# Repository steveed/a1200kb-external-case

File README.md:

# A1200KB external case

Run an [A1200KBv2](https://github.com/aeberbach/A1200KBv2) mechanical keyboard in its own external case, connected by cable to an A1200 motherboard in a case with no built-in keyboard, such as the Checkmate 1500 Plus.

Normally an external case means a PS/2 or USB keyboard and an adapter. This project keeps the real A1200 keyboard instead.

**Setting one up, or stuck?** The [setup guide](docs/Readme.md) shows each way of connecting, what (if anything) has to change on the A1200, the cable wiring, and a troubleshooting table.

## How it works

The A1200 keyboard has no controller of its own. It is a bare switch matrix scanned by the keyboard controller on the motherboard, so every one of the 31 lines on the keyboard ribbon (FFC) has to reach the motherboard. DB25 has too few pins, so this uses DB37:

```
A1200 motherboard ── FFC ── [adapter] ══ DB37 cable ══ [adapter] ── FFC ── A1200KBv2 keyboard
     LED header ──────────── J2                         J2 ──────────────── keyboard LED header
```

Both ends use the same adapter board. See [`adapter/Readme.md`](adapter/Readme.md) for the pinout, build options and parts.

### Alternative: standard Amiga keyboard (DIN 5)

On A1200 boards with the CN17 "KB TEST" header, the keyboard controller's serial lines are available directly:

```
A1200KBv2 ── [encoder] ══ DIN 5 cable ══ [din5 board] ── A1200 CN17
```

- [`din5/`](din5/Readme.md) gives the A1200 a standard 5-pin DIN keyboard socket. An A2000/A3000 keyboard (or an A4000 one through a PS/2-to-AT adapter) plugs straight in. No firmware.
- [`encoder/`](encoder/Readme.md) turns the A1200KBv2 into a standard Amiga keyboard with that same DIN 5, so it also works on an A2000/A3000. It has the same outline as the DB37 adapter, so either fits the case. The activity LEDs don't come across; the power LED does.
- Or plug an A1200 keyboard into an Amiga keyboard controller board from an A500/A2000-style keyboard, and run that board's DIN 5 cable to the din5 board.
- No CN17? A clip on U13 picks up the same signals without soldering. See the [setup guide](docs/Readme.md).

## Contents

- `adapter/` — KiCad 10 project for the FFC ⇄ DB37 adapter board, with Gerbers in `adapter/fab/`
- `encoder/` — KiCad 10 project for the A1200KBv2 to Amiga keyboard (DIN 5) encoder, with Gerbers in `encoder/fab/`
- `din5/` — KiCad 10 project for the A1200 standard keyboard socket (CN17 to DIN 5), with Gerbers in `din5/fab/`
- `lib/A1200KB.pretty` — footprints shared by those boards (DIN 5)
- `case/` — OpenSCAD model of the keyboard case (see [`case/Readme.md`](case/Readme.md))
- `docs/` — setup guide, wiring diagrams and renders (`docs/render.sh` regenerates the images)

## Status

Rev 1 of the adapter is designed but not built or tested. The encoder and din5 boards are designed and routed; the encoder has no firmware yet. Before ordering adapter boards:

- Check the DB37 footprint against the connector you buy.
- Choose the ESD diodes (low capacitance, about 50pF or less).
- Hand-wire a test rig with DB37 screw-terminal breakouts to confirm the A1200 scans the matrix reliably over the full cable length.

## License

CC-BY-NC-SA 4.0, the same as A1200KBv2, whose FFC footprint this reuses. See `LICENSE`.

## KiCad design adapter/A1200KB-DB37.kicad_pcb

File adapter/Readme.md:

A1200 keyboard FFC to DB37 adapter, for running an A1200KBv2 keyboard in an external case (e.g. with a Checkmate 1500 Plus).

The A1200 keyboard is a bare matrix scanned by the keyboard controller on the motherboard, so all 31 FFC lines have to travel down the cable. DB25 is too small; DB37 carries them plus the LED header and ground.

One board design is used at both ends:

- Amiga end: FFC from the motherboard keyboard connector to J1, DB37 on the rear panel.
- Keyboard end: FFC from the keyboard's J1 to this board's J1, DB37 on the keyboard case.
- Join the two with a straight-through, fully wired, shielded DB37 **male-male** cable (both boards have female sockets).

DB37 pinout:

- FFC pin n (odd) -> DB37 pin (n+1)/2, FFC pin n (even) -> DB37 pin 19+n/2. FFC 9 is VCC (through F1), FFC 31 is /CAPSLOCK, FFC 32 unused.
- DB37 17 DISK LED, 18 FLOPPY LED, 19 PWR LED, 35-37 GND.
- J2 (LED header, right-angle 1x5): 1 GND, 2 PWR, 3 FLOPPY, 4 DISK, 5 GND. Pins 1-4 match the keyboard's 4-pin J2.

J2 is symmetric on purpose. A reversed plug keeps GND on GND and FLOPPY in the middle; only the PWR and DISK LEDs swap, so nothing is damaged. A plain 4-pin pinout reversed would put an LED output on ground and reverse-power the keyboard's LED inverter (U1). Only the adapter end is protected this way: the far ends of the jumper cables (A1200 LED header, keyboard J2) can still be plugged in backwards.

The A1200 keyboard FFC has no ground pin, so ground only reaches the board through J2. Wire the A1200 LED header to J2 on the Amiga-side board and the keyboard's J2 to J2 on the keyboard-side board (pins 1-4; pin 5 is a spare GND), or the LEDs and ESD diodes have no return. If the case's own LEDs already use the A1200 LED header, use a Y-split cable.

The A1200 LED header (CN14) does not share this pinout: it is 1 PWR, 2 FLOPPY, 3 IDE, 4 CC (unused), 5 GND, and pins 1-4 are driven high straight from VCC. Do not use a straight cable on the Amiga side, or CN14 pin 1 (the power LED driver) lands on J2's GND. Wire CN14 1 → J2 2, CN14 2 → J2 3, CN14 3 → J2 4, CN14 5 → J2 1.

Build options:

- Amiga-side board: fit D1-D34 (SOD-323 5V ESD diodes, keep capacitance low, around 50pF or less) and close JP1 to ground the shell.
- Keyboard-side board: D1-D34 optional, leave JP1 open so the shell is grounded at one end only.
- F1: 1206 PTC, about 100mA hold. VCC only feeds the Caps Lock LED.

Parts:

- J1: Molex 52044-3245, 32-way 1.25mm RA FFC connector (same as the keyboard)
- J3: DB37 female right-angle PCB mount, the common "7.2mm" type: about 8.1mm from the flange to the nearest pin row, 63.5mm mounting holes (CONNFLY DS1037-37FNAKT74-0CC, LCSC C77839). The board edge sits 7.7mm from that row, so the flange overhangs the edge slightly instead of the board poking out past it. Check the footprint against the part you buy.
- J2: 1x5 2.54mm right-angle pin header. Its pins stick out past the top edge, on the same side as the FFC.
- FFC cables: 31-way 1.25mm. Use the same contact type as the keyboard's cable, then check with a meter that FFC pin 1 reaches DB37 pin 1 on each board before powering up.

JLCPCB assembly:

- Upload the gerber zip of `fab/` (gerbers and drill), then `fab/A1200KB-DB37-bom.csv` and `fab/A1200KB-DB37-cpl.csv`. Both come from `jlc-export.sh` (run from the repo root).
- The diodes are on the bottom and F1 is on the top, so it needs two-sided Standard PCBA, with through-hole assembly for J1-J3.
- LCSC parts: D1-D34 C19224, F1 C70065, J2 C32713264, J3 C77839. J1 (Molex 52044-3245) isn't stocked at LCSC; the BOM gives the MPN for JLC's global sourcing.
- D1-D34 are bidirectional, so a 180° rotation in JLC's preview doesn't matter. Check the J3 and J2 rotations in the preview.
- This fits the diodes on every board; on keyboard-side boards they are harmless. JP1 is a solder jumper: bridge it by hand on the Amiga-side boards.

Don't plug or unplug the cable with the Amiga powered.

License: CC-BY-NC-SA 4.0

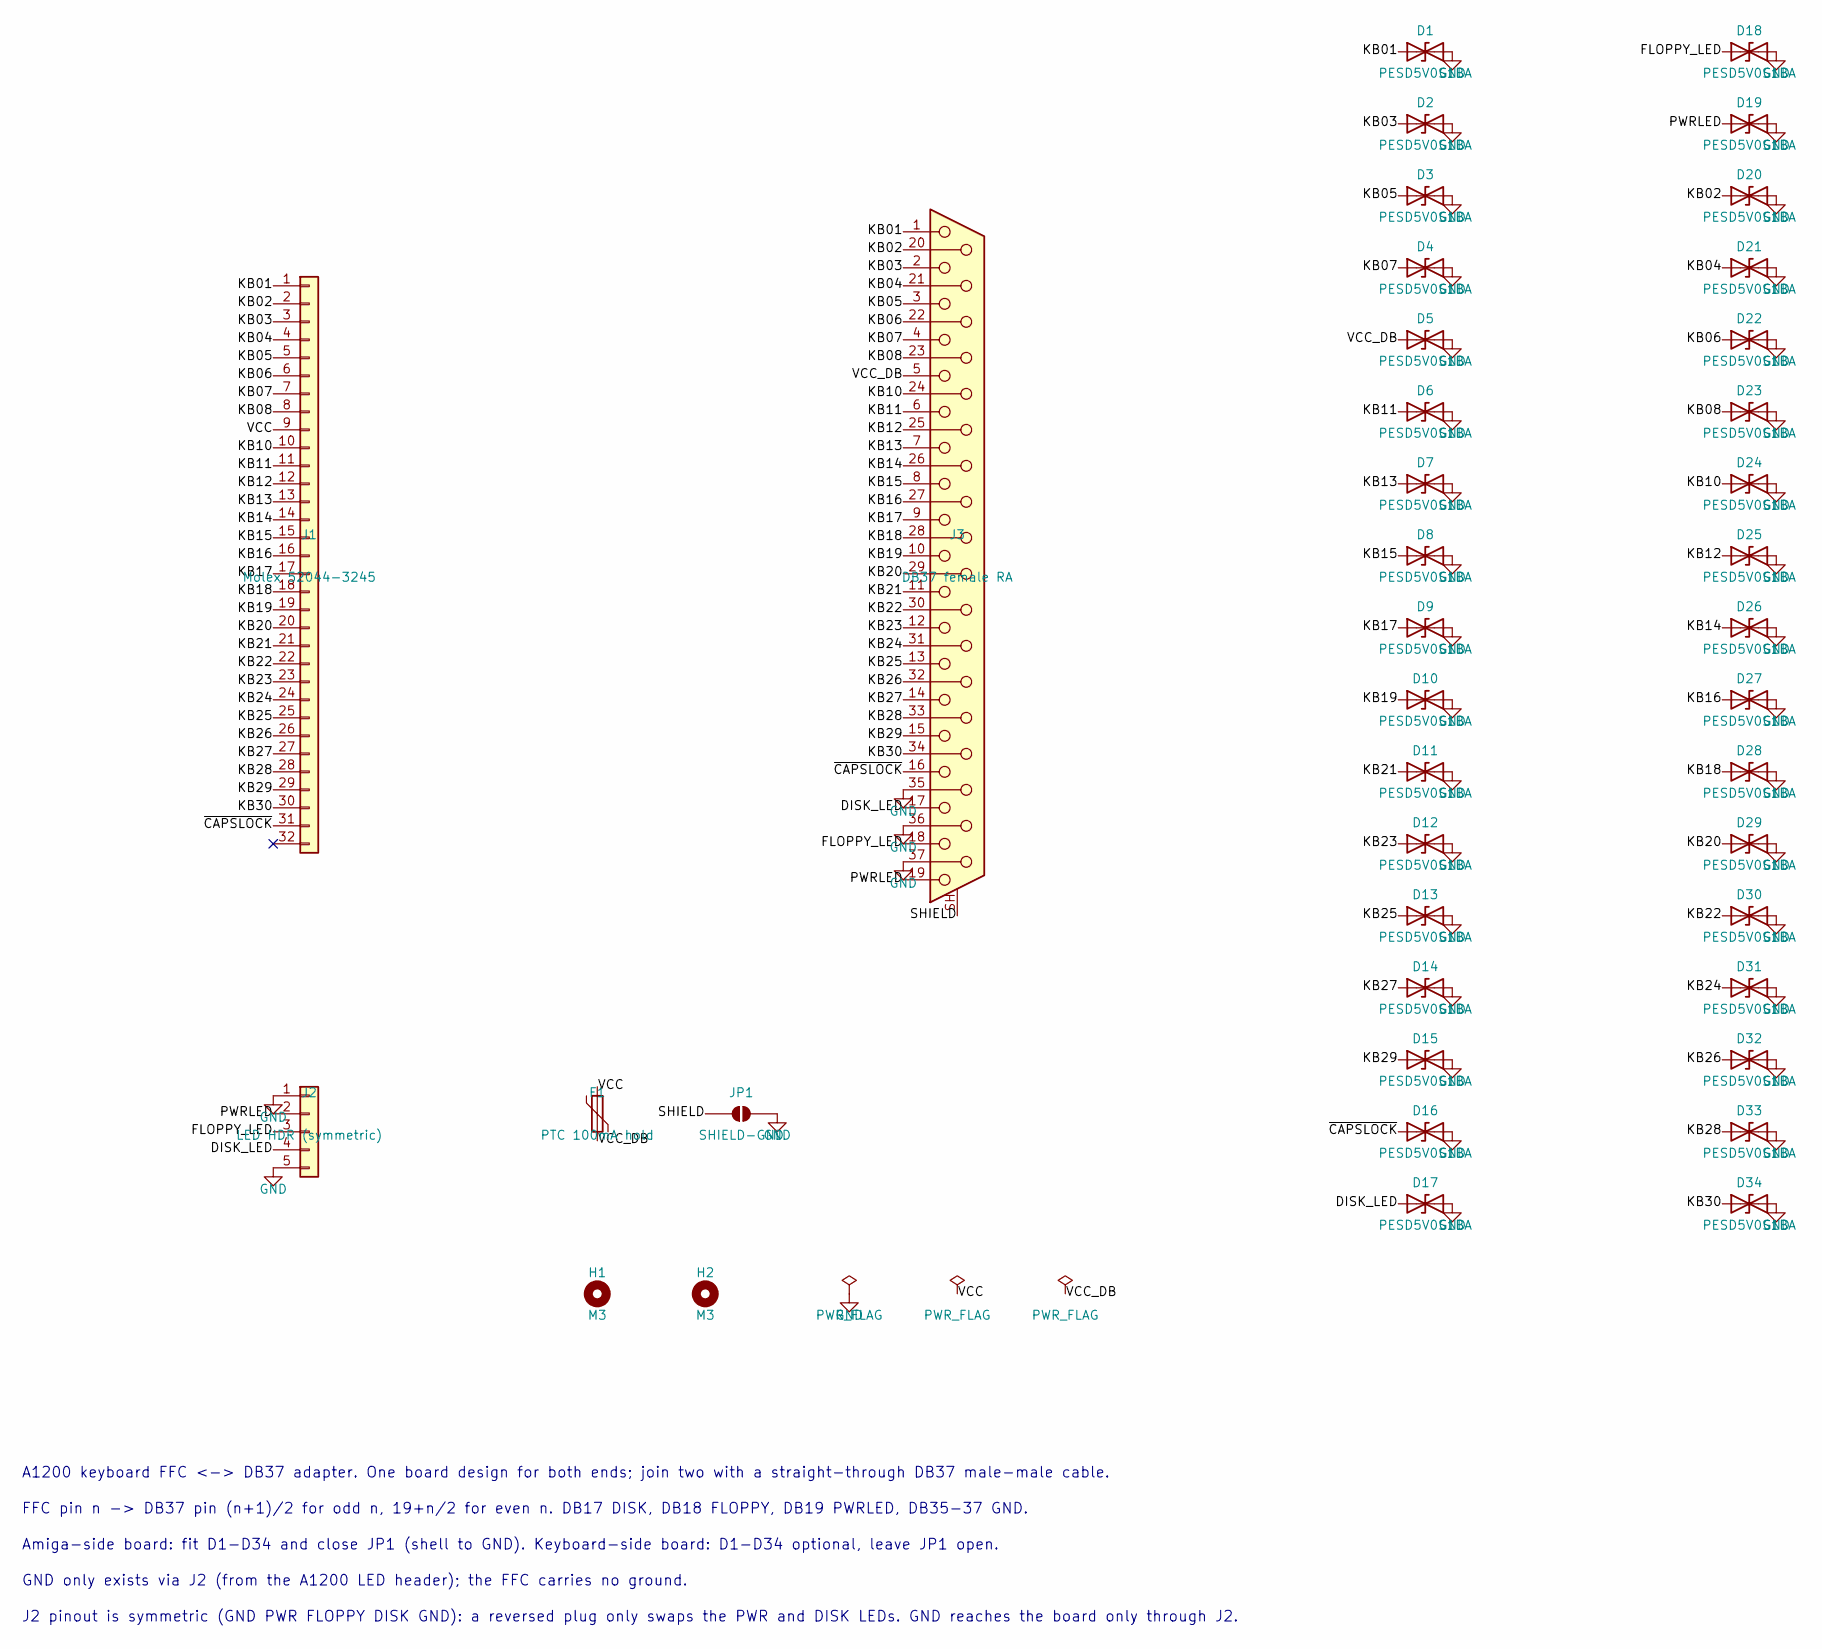
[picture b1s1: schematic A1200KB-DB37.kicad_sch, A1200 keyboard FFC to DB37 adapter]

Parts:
D1, D2, D3, D4, D5, D6, D7, D8, D9, D10, D11, D12, D13, D14, D15, D16, D17, D18, D19, D20, D21, D22, D23, D24, D25, D26, D27, D28, D29, D30, D31, D32, D33, D34: PESD5V0S1BA; D_SOD-323; MPN PESD5V0S1BA,115; LCSC C19224
F1: PTC 100mA hold; Fuse_1206_3216Metric; MPN nSMD010; LCSC C70065
H1, H2: M3; MountingHole_3.2mm_M3
J1: Molex 52044-3245; FFC-1.25mm-RA-5204403245; MPN 52044-3245
J2: LED HDR (symmetric); PinHeader_1x05_P2.54mm_Horizontal; MPN HX PZ2.54-1x5P WZ; LCSC C32713264
J3: DB37 female RA; DSUB-37_Socket_Horizontal_P2.77x2.84mm_EdgePinOffset7.70mm_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; MPN DS1037-37FNAKT74-0CC; LCSC C77839
JP1: SHIELD-GND; SolderJumper-2_P1.3mm_Open_RoundedPad1.0x1.5mm

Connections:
/DISK_LED: D17.1 (A1), J2.4, J3.17
/FLOPPY_LED: D18.1 (A1), J2.3, J3.18
/KB01: D1.1 (A1), J1.1, J3.1
/KB02: D20.1 (A1), J1.2, J3.20
/KB03: D2.1 (A1), J1.3, J3.2
/KB04: D21.1 (A1), J1.4, J3.21
/KB05: D3.1 (A1), J1.5, J3.3
/KB06: D22.1 (A1), J1.6, J3.22
/KB07: D4.1 (A1), J1.7, J3.4
/KB08: D23.1 (A1), J1.8, J3.23
/KB10: D24.1 (A1), J1.10, J3.24
/KB11: D6.1 (A1), J1.11, J3.6
/KB12: D25.1 (A1), J1.12, J3.25
/KB13: D7.1 (A1), J1.13, J3.7
/KB14: D26.1 (A1), J1.14, J3.26
/KB15: D8.1 (A1), J1.15, J3.8
/KB16: D27.1 (A1), J1.16, J3.27
/KB17: D9.1 (A1), J1.17, J3.9
/KB18: D28.1 (A1), J1.18, J3.28
/KB19: D10.1 (A1), J1.19, J3.10
/KB20: D29.1 (A1), J1.20, J3.29
/KB21: D11.1 (A1), J1.21, J3.11
/KB22: D30.1 (A1), J1.22, J3.30
/KB23: D12.1 (A1), J1.23, J3.12
/KB24: D31.1 (A1), J1.24, J3.31
/KB25: D13.1 (A1), J1.25, J3.13
/KB26: D32.1 (A1), J1.26, J3.32
/KB27: D14.1 (A1), J1.27, J3.14
/KB28: D33.1 (A1), J1.28, J3.33
/KB29: D15.1 (A1), J1.29, J3.15
/KB30: D34.1 (A1), J1.30, J3.34
/PWRLED: D19.1 (A1), J2.2, J3.19
/SHIELD: J3.SH (PAD), JP1.1 (A)
/VCC: F1.1, J1.9
/VCC_DB: D5.1 (A1), F1.2, J3.5
/~CAPSLOCK: D16.1 (A1), J1.31, J3.16
GND: D1.2 (A2), D2.2 (A2), D3.2 (A2), D4.2 (A2), D5.2 (A2), D6.2 (A2), D7.2 (A2), D8.2 (A2), D9.2 (A2), D10.2 (A2), D11.2 (A2), D12.2 (A2), D13.2 (A2), D14.2 (A2), D15.2 (A2), D16.2 (A2), D17.2 (A2), D18.2 (A2), D19.2 (A2), D20.2 (A2), D21.2 (A2), D22.2 (A2), D23.2 (A2), D24.2 (A2), D25.2 (A2), D26.2 (A2), D27.2 (A2), D28.2 (A2), D29.2 (A2), D30.2 (A2), D31.2 (A2), D32.2 (A2), D33.2 (A2), D34.2 (A2), J2.1, J2.5, J3.35, J3.36, J3.37, JP1.2 (B)

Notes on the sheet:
FFC pin n -> DB37 pin (n+1)/2 for odd n, 19+n/2 for even n. DB17 DISK, DB18 FLOPPY, DB19 PWRLED, DB35-37 GND.
Amiga-side board: fit D1-D34 and close JP1 (shell to GND). Keyboard-side board: D1-D34 optional, leave JP1 open.
GND only exists via J2 (from the A1200 LED header); the FFC carries no ground.
A1200 keyboard FFC <-> DB37 adapter. One board design for both ends; join two with a straight-through DB37 male-male cable.
J2 pinout is symmetric (GND PWR FLOPPY DISK GND): a reversed plug only swaps the PWR and DISK LEDs. GND reaches the board only through J2.

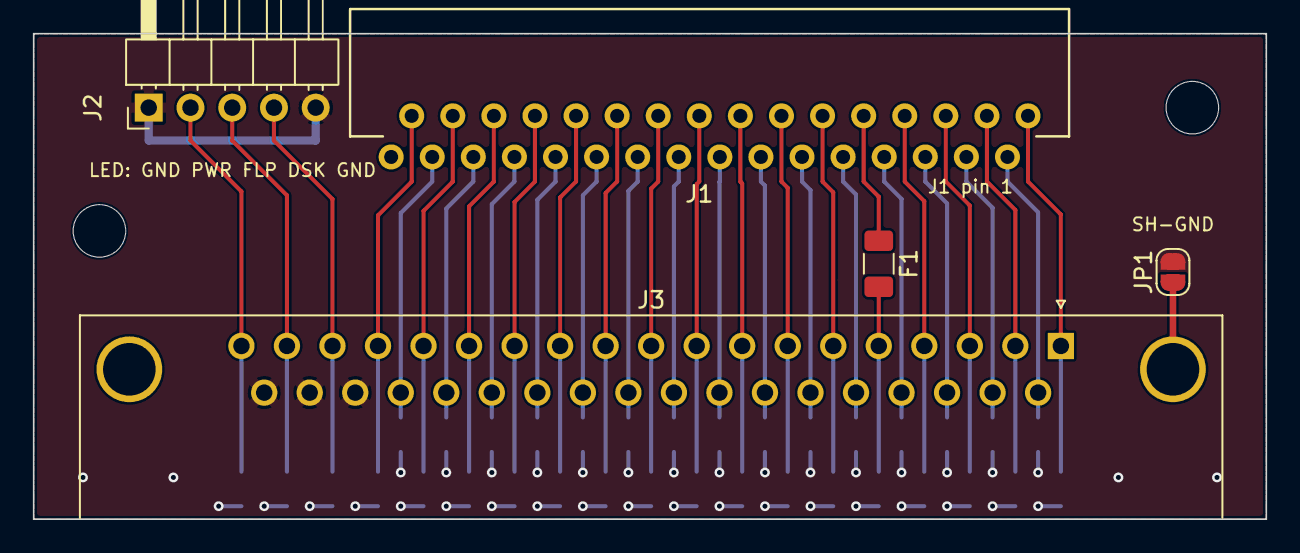
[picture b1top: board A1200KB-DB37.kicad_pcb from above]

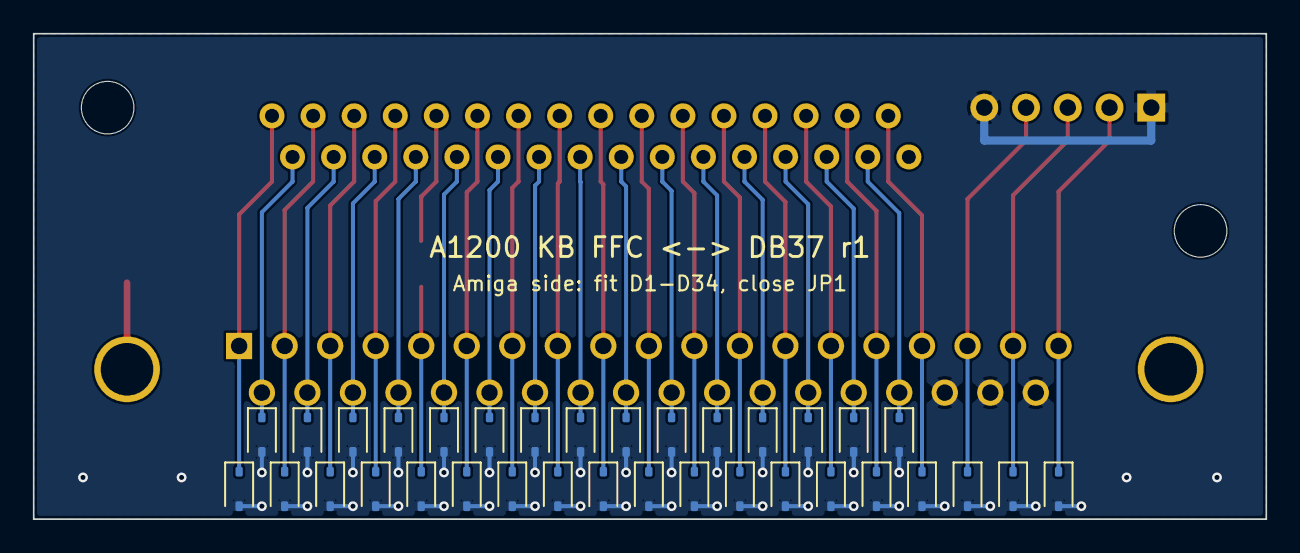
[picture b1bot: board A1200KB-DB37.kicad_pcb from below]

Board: 2 copper layers, 75.0 x 29.5 mm, 41 parts (34 on the bottom side), 37 nets.

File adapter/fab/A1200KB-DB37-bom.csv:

"Comment","Designator","Footprint","LCSC Part #","MPN"
"PESD5V0S1BA","D1,D2,D3,D4,D5,D6,D7,D8,D9,D10,D11,D12,D13,D14,D15,D16,D17,D18,D19,D20,D21,D22,D23,D24,D25,D26,D27,D28,D29,D30,D31,D32,D33,D34","Diode_SMD:D_SOD-323","C19224","PESD5V0S1BA,115"
"PTC 100mA hold","F1","Fuse:Fuse_1206_3216Metric","C70065","nSMD010"
"Molex 52044-3245","J1","Amiga_FFC:FFC-1.25mm-RA-5204403245","","52044-3245"
"LED HDR (symmetric)","J2","Connector_PinHeader_2.54mm:PinHeader_1x05_P2.54mm_Horizontal","C32713264","HX PZ2.54-1x5P WZ"
"DB37 female RA","J3","Connector_Dsub:DSUB-37_Socket_Horizontal_P2.77x2.84mm_EdgePinOffset7.70mm_Housed_MountingHolesOffset9.12mm","C77839","DS1037-37FNAKT74-0CC"

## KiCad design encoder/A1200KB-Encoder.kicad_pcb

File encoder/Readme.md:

# Encoder: A1200KBv2 as a standard Amiga keyboard

An alternative to the DB37 adapters. An ATmega4809 in the keyboard case scans the A1200KBv2 matrix and speaks the Amiga keyboard protocol on a standard 5-pin DIN, like an A2000 or A3000 keyboard. Plug it into an A1200 fitted with the [`din5`](../din5/Readme.md) board, or straight into an A2000/A3000.

```
A1200KBv2 ── FFC + J2 ── [encoder] ══ DIN 5 cable ══ [din5 board] ── A1200 CN17
                                                  or  A2000 / A3000 keyboard port
```

## DIN 5 pinout

Same as an A2000/A3000 keyboard port: 1 KCLK, 2 KDAT, 3 NC, 4 GND (and the shell), 5 +5V. Use a straight-through male-to-male 5-pin DIN cable with all five pins wired; some MIDI cables only wire three.

## LEDs

The DIN has no LED lines, so the floppy and disk activity LEDs don't work. U1 drives the keyboard's LED header instead:

- PWR (PF1): on whenever the keyboard has power. It also powers the keyboard's Caps Lock LED inverter, so it must be on for the power LED to turn blue with Caps Lock. The A1200's dimmed power LED (audio filter off) is lost.
- FLOPPY (PF2), DISK (PF3): wired but unused; the firmware can use them for anything.
- Caps Lock: handled by the encoder, as on any Amiga keyboard.

## Board

Same outline, mounting holes, J1 and J2 positions as the DB37 adapter, so it fits the case in the same place (`link="din5"` in `case/a1200kb-case.scad` gives the round rear cut-out).

- U1: ATmega4809 (TQFP-48), on its internal oscillator.
- J1: Molex 52044-3245 FFC, as on the adapter. Hand-solder it, or use JLC global sourcing.
- J2: LED header to the keyboard's J2, symmetric as on the adapter: 1 GND, 2 PWR, 3 FLOPPY, 4 DISK, 5 GND.
- J3: DIN-504 5-pin 180° socket (LCSC C23689428), its face on the rear edge, centred at x 134. The footprint in `lib/A1200KB.pretty` is drawn from the datasheet.
- J4: UPDI programming header (1 UPDI, 2 +5V, 3 GND, 4 TXD debug). Not fitted by JLC; solder it yourself or use pogo pins.
- KCLK and KDAT go out through 100Ω with 10k pull-ups and ESD diodes.
- R5 (150Ω) sets the Caps Lock LED current; the keyboard's LED anode is on VCC and U1 sinks it.

## Matrix wiring

The keyboard matrix has no diodes: 6 rows and 7 modifiers against 16 columns. The firmware drives one column low at a time and reads the other 13 lines with pull-ups enabled.

- FFC 1-5, 7 (rows): PA2-PA7
- FFC 6, 8, 10-14 (modifiers): PB0-PB5, PE0
- FFC 15-22 (columns): PD0-PD7; FFC 23-30: PC0-PC7
- FFC 9: VCC; FFC 31: /CAPSLOCK through R5 to PF0
- KCLK PE1, KDAT PE2, debug TXD PA0

## Firmware

Not written yet. It needs to:

- scan the matrix and block ghost keys, as the original keyboard controller does (no diodes)
- send keycodes with the Amiga keyboard protocol: the power-up stream, the handshake, resync, Caps Lock toggling its own LED
- on Ctrl-Amiga-Amiga, send the reset warning, then hold KCLK low for 500ms (the din5 board turns that into the A1200's KB_RESET)
- turn the power LED on at start-up

## Fab files

`fab/` has Gerbers, drill and the JLC BOM and CPL. Regenerate after any change (see the checks in `CLAUDE.md`).

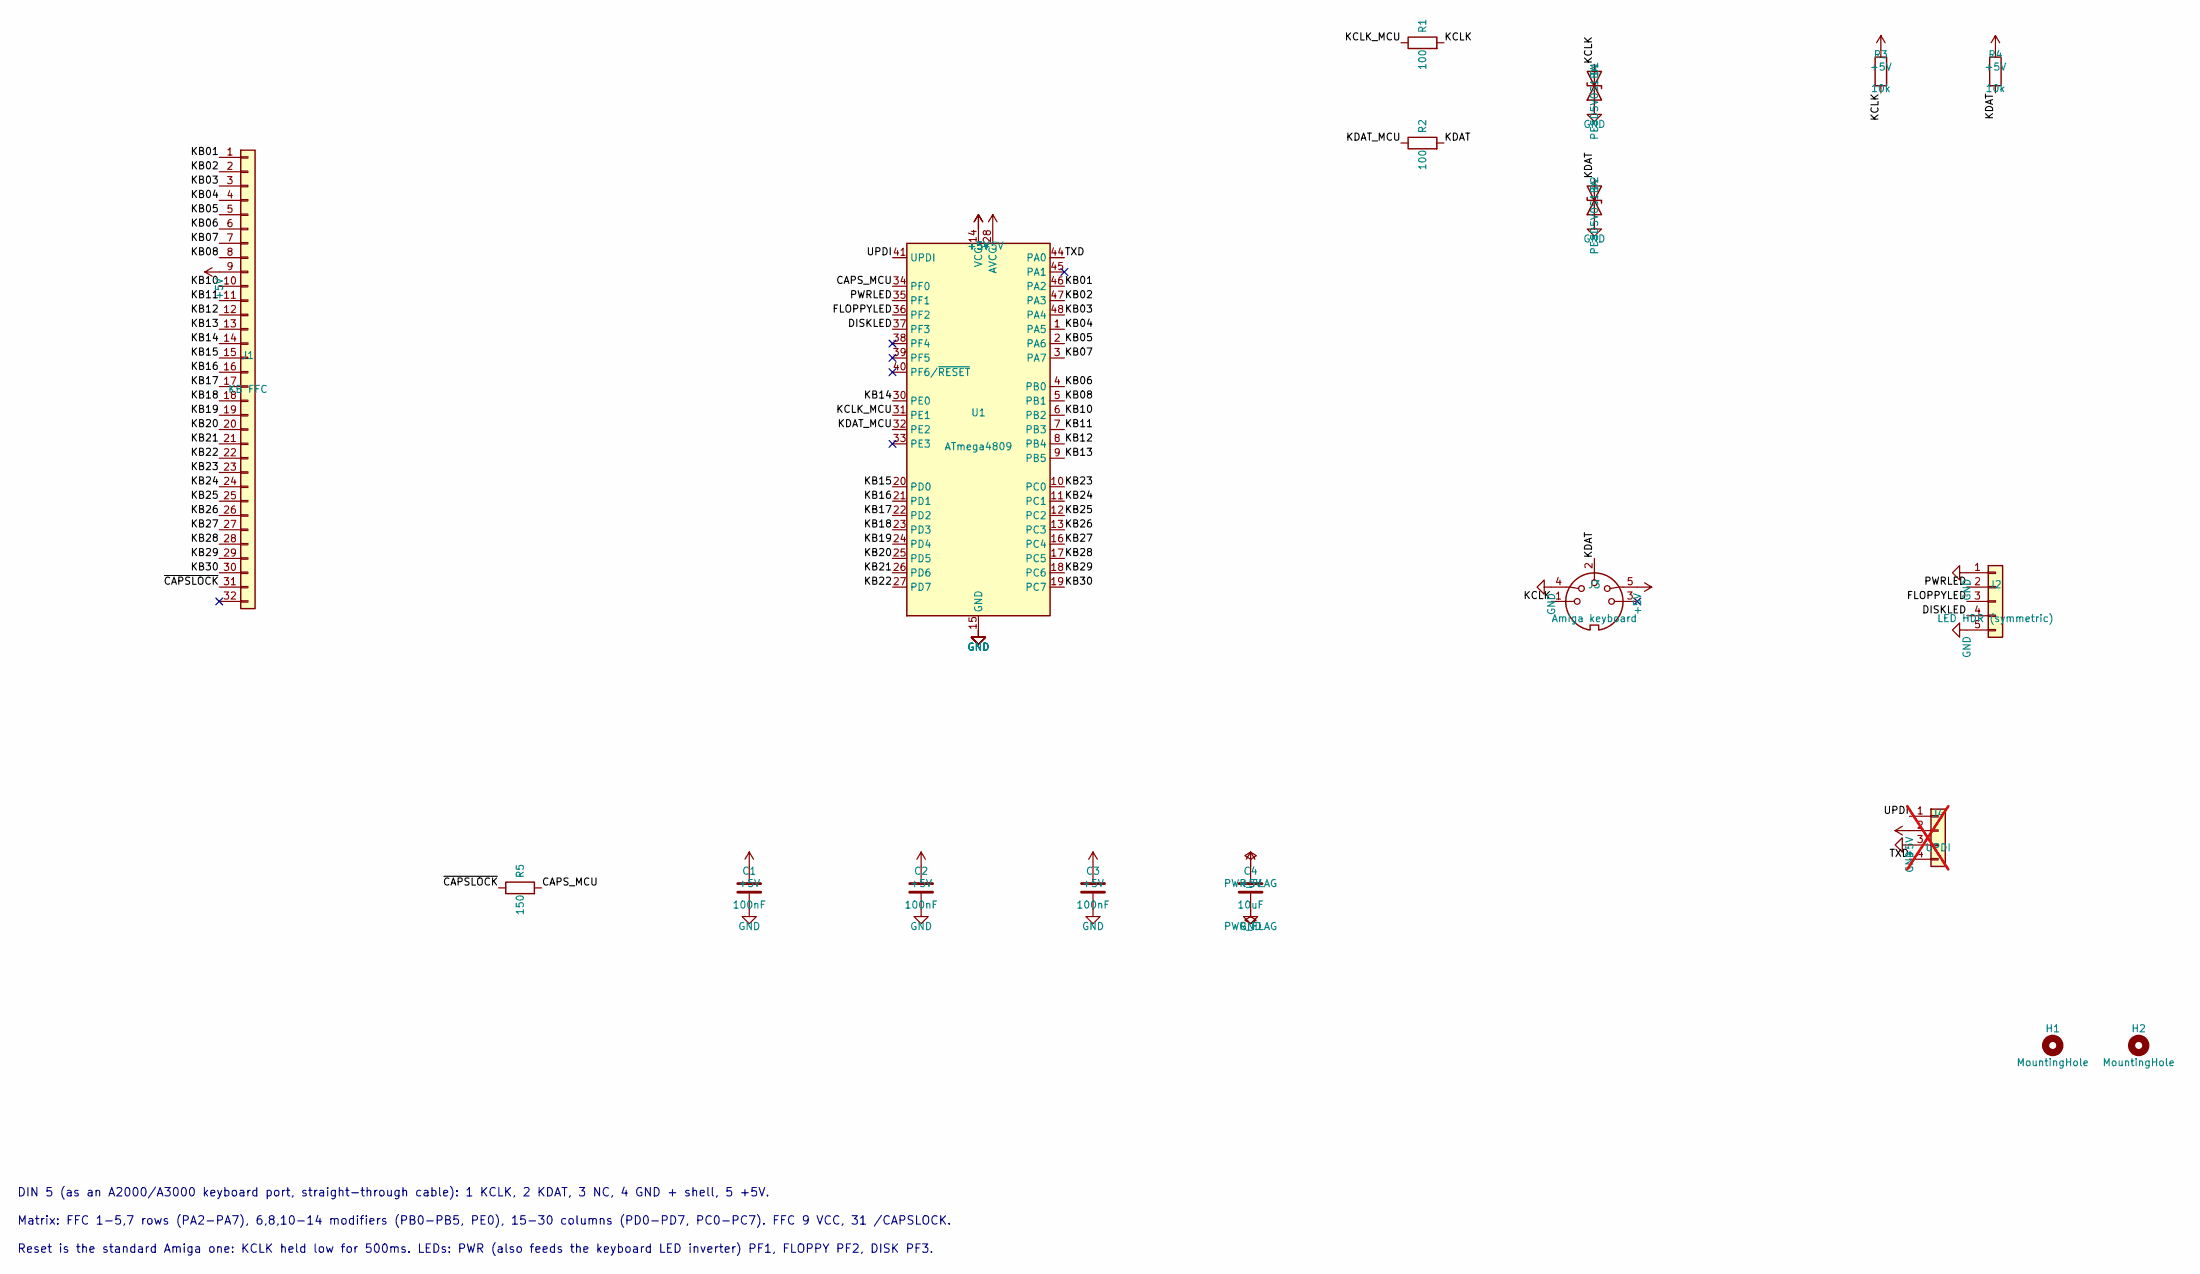
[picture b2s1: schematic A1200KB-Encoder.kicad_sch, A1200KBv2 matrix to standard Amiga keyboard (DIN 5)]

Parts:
C1, C2, C3: 100nF; C_0603_1608Metric; MPN CC0603KRX7R9BB104; LCSC C14663
C4: 10uF; C_0805_2012Metric; MPN CL21A106KAYNNNE; LCSC C15850
D1, D2: PESD5V0S1BA; D_SOD-323; MPN PESD5V0S1BA,115; LCSC C19224
H1, H2: MountingHole; MountingHole_3.2mm_M3
J1: KB FFC; FFC-1.25mm-RA-5204403245; MPN 52044-3245
J2: LED HDR (symmetric); PinHeader_1x05_P2.54mm_Horizontal; MPN HX PZ2.54-1x5P WZ; LCSC C32713264
J3: Amiga keyboard; DIN-5_180deg_DIN-504_Horizontal; MPN DIN-504; LCSC C23689428
J4: UPDI; PinHeader_1x04_P2.54mm_Vertical; not fitted
R1, R2: 100; R_0603_1608Metric; MPN 0603WAF1000T5E; LCSC C22775
R3, R4: 10k; R_0603_1608Metric; MPN 0603WAF1002T5E; LCSC C25804
R5: 150; R_0603_1608Metric; MPN 0603WAF1500T5E; LCSC C22808
U1: ATmega4809; TQFP-48_7x7mm_P0.5mm; MPN ATMEGA4809-AFR; LCSC C189475

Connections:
+5V: C1.1, C2.1, C3.1, C4.1, J1.9, J3.5, J4.2, R3.1, R4.1, U1.14 (VCC), U1.28 (AVCC), U1.42 (VCC)
/CAPS_MCU: R5.2, U1.34 (PF0)
/DISKLED: J2.4, U1.37 (PF3)
/FLOPPYLED: J2.3, U1.36 (PF2)
/KB01: J1.1, U1.46 (PA2)
/KB02: J1.2, U1.47 (PA3)
/KB03: J1.3, U1.48 (PA4)
/KB04: J1.4, U1.1 (PA5)
/KB05: J1.5, U1.2 (PA6)
/KB06: J1.6, U1.4 (PB0)
/KB07: J1.7, U1.3 (PA7)
/KB08: J1.8, U1.5 (PB1)
/KB10: J1.10, U1.6 (PB2)
/KB11: J1.11, U1.7 (PB3)
/KB12: J1.12, U1.8 (PB4)
/KB13: J1.13, U1.9 (PB5)
/KB14: J1.14, U1.30 (PE0)
/KB15: J1.15, U1.20 (PD0)
/KB16: J1.16, U1.21 (PD1)
/KB17: J1.17, U1.22 (PD2)
/KB18: J1.18, U1.23 (PD3)
/KB19: J1.19, U1.24 (PD4)
/KB20: J1.20, U1.25 (PD5)
/KB21: J1.21, U1.26 (PD6)
/KB22: J1.22, U1.27 (PD7)
/KB23: J1.23, U1.10 (PC0)
/KB24: J1.24, U1.11 (PC1)
/KB25: J1.25, U1.12 (PC2)
/KB26: J1.26, U1.13 (PC3)
/KB27: J1.27, U1.16 (PC4)
/KB28: J1.28, U1.17 (PC5)
/KB29: J1.29, U1.18 (PC6)
/KB30: J1.30, U1.19 (PC7)
/KCLK: D1.2 (A2), J3.1, R1.2, R3.2
/KCLK_MCU: R1.1, U1.31 (PE1)
/KDAT: D2.2 (A2), J3.2, R2.2, R4.2
/KDAT_MCU: R2.1, U1.32 (PE2)
/PWRLED: J2.2, U1.35 (PF1)
/TXD: J4.4, U1.44 (PA0)
/UPDI: J4.1, U1.41 (UPDI)
/~CAPSLOCK: J1.31, R5.1
GND: C1.2, C2.2, C3.2, C4.2, D1.1 (A1), D2.1 (A1), J2.1, J2.5, J3.4, J4.3, U1.15 (GND), U1.29 (GND), U1.43 (GND)

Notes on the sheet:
DIN 5 (as an A2000/A3000 keyboard port, straight-through cable): 1 KCLK, 2 KDAT, 3 NC, 4 GND + shell, 5 +5V.
Matrix: FFC 1-5,7 rows (PA2-PA7), 6,8,10-14 modifiers (PB0-PB5, PE0), 15-30 columns (PD0-PD7, PC0-PC7). FFC 9 VCC, 31 /CAPSLOCK.
Reset is the standard Amiga one: KCLK held low for 500ms. LEDs: PWR (also feeds the keyboard LED inverter) PF1, FLOPPY PF2, DISK PF3.

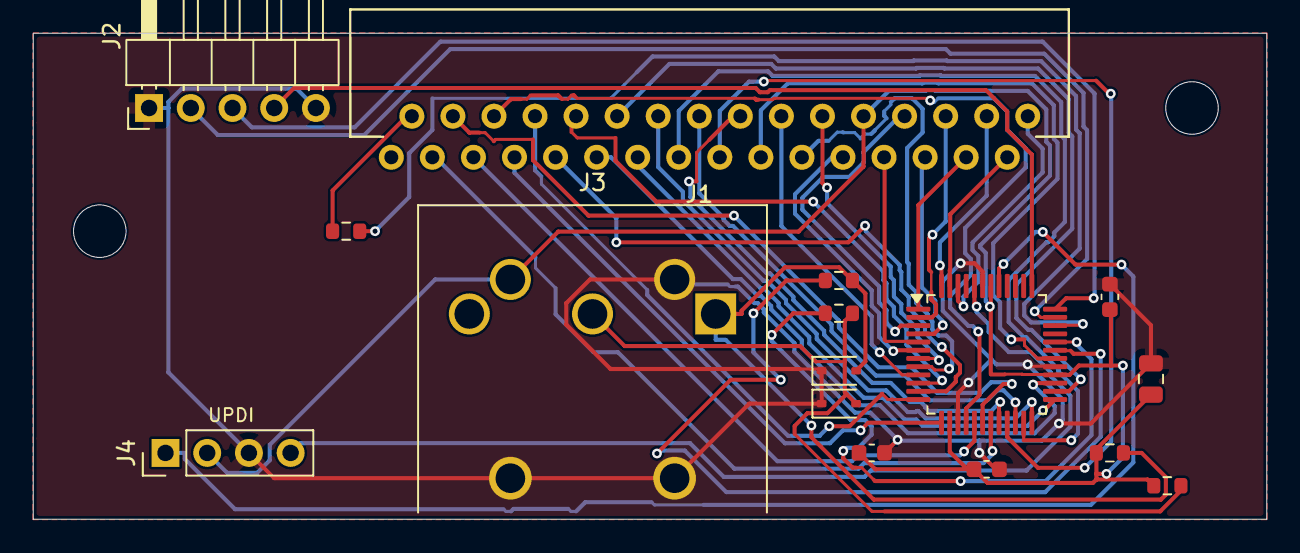
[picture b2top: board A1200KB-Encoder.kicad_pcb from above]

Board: 2 copper layers, 75.1 x 29.6 mm, 18 parts (0 on the bottom side), 42 nets.

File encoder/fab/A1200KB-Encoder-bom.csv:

"Comment","Designator","Footprint","LCSC Part #","MPN"
"100nF","C1,C2,C3","Capacitor_SMD:C_0603_1608Metric","C14663","CC0603KRX7R9BB104"
"10uF","C4","Capacitor_SMD:C_0805_2012Metric","C15850","CL21A106KAYNNNE"
"PESD5V0S1BA","D1,D2","Diode_SMD:D_SOD-323","C19224","PESD5V0S1BA,115"
"KB FFC","J1","Amiga_FFC:FFC-1.25mm-RA-5204403245","","52044-3245"
"LED HDR (symmetric)","J2","Connector_PinHeader_2.54mm:PinHeader_1x05_P2.54mm_Horizontal","C32713264","HX PZ2.54-1x5P WZ"
"Amiga keyboard","J3","A1200KB:DIN-5_180deg_DIN-504_Horizontal","C23689428","DIN-504"
"100","R1,R2","Resistor_SMD:R_0603_1608Metric","C22775","0603WAF1000T5E"
"10k","R3,R4","Resistor_SMD:R_0603_1608Metric","C25804","0603WAF1002T5E"
"150","R5","Resistor_SMD:R_0603_1608Metric","C22808","0603WAF1500T5E"
"ATmega4809","U1","Package_QFP:TQFP-48_7x7mm_P0.5mm","C189475","ATMEGA4809-AFR"

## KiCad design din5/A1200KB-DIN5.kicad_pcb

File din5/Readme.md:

# A1200 standard keyboard socket (DIN 5)

A small board for A1200s with the CN17 "KB TEST" header: it gives the A1200 a standard Amiga 5-pin DIN keyboard socket, the same as an A2000 or A3000. No firmware.

- An A2000 or A3000 keyboard plugs straight in.
- An A4000 keyboard (6-pin mini-DIN) works through a standard passive PS/2-to-AT adapter; the pinouts line up the same way as on a PC.
- The A1200KBv2 plugs in through the [`encoder`](../encoder/Readme.md).
- An A1200 keyboard works through an Amiga keyboard controller board (see setup D in the [setup guide](../docs/Readme.md)).

```
A1200 CN17 ── [din5 board] ── DIN 5 socket ── any Amiga keyboard
```

## CN17

CN17 brings out the onboard keyboard controller's serial lines. The A1200 schematic marks it "new on Rev 1E PCB": check your board for a 7-pin header near the keyboard ribbon connector. On some boards the pads are there but the header isn't fitted.

| CN17 pin | Signal |
|----------|--------|
| 1 | KB_DATA |
| 2 | KB_CLOCK |
| 3 | KB_RESET |
| 4 | Reset input of U13, the A1200's keyboard controller |
| 5 | NC |
| 6 | VCC |
| 7 | GND |

No CN17 on your board? A PLCC clip on U13 can bring the same signals out on a CN17-order header; the [setup guide](../docs/Readme.md#no-cn17-clip-onto-u13) has the pin mapping.

JP1 (bridged) ties CN17 pin 4 to ground so the A1200's own keyboard controller (U13) stays in reset and lets go of the clock and data lines. Cut JP1 to give it back.

## DIN 5 pinout

Female socket, front view: 3 and 1 across, 5 and 4 on the diagonals, 2 at the bottom.

| Pin | Signal |
|-----|--------|
| 1 | KCLK |
| 2 | KDAT |
| 3 | NC |
| 4 | GND, and the shell |
| 5 | +5V (through F1, 500mA hold) |

## Reset

The A1200 normally gets Ctrl-Amiga-Amiga from U13 on KB_RESET. A standard Amiga keyboard instead sends a reset warning and then holds KCLK low for 500ms. R1 (220k) and C1 (1µF) only discharge during such a long low (normal clock pulses are microseconds), and U1 (74LVC1G14 Schmitt inverter) then drives KB_RESET through R2 after about 225ms. The same RC holds KB_RESET for a moment at power-on, which is harmless.

KB_RESET is taken as active-high, because the A1200 pulls it down with 10k (R623). If it proves active-low, fit a 74LVC1G17 for U1: same SOT-353 package and pinout, non-inverting.

## Parts

- J1: 1x7 2.54mm vertical header (C492406), cabled to CN17.
- J2: DIN-504 5-pin 180° right-angle socket (C23689428), face on the board edge. Footprint drawn from the datasheet in `lib/A1200KB.pretty`.
- F1: 500mA hold PTC (C69688). Original Amiga keyboards draw more than the A1200KBv2.
- D1, D2: PESD5V0S1BA (C19224) on KCLK and KDAT.
- U1, R1, R2, C1, C2: the reset timer.
- JP1: bridged solder jumper.

The A1200 LED header (CN14) isn't used: the LEDs stay with the A1200's case.

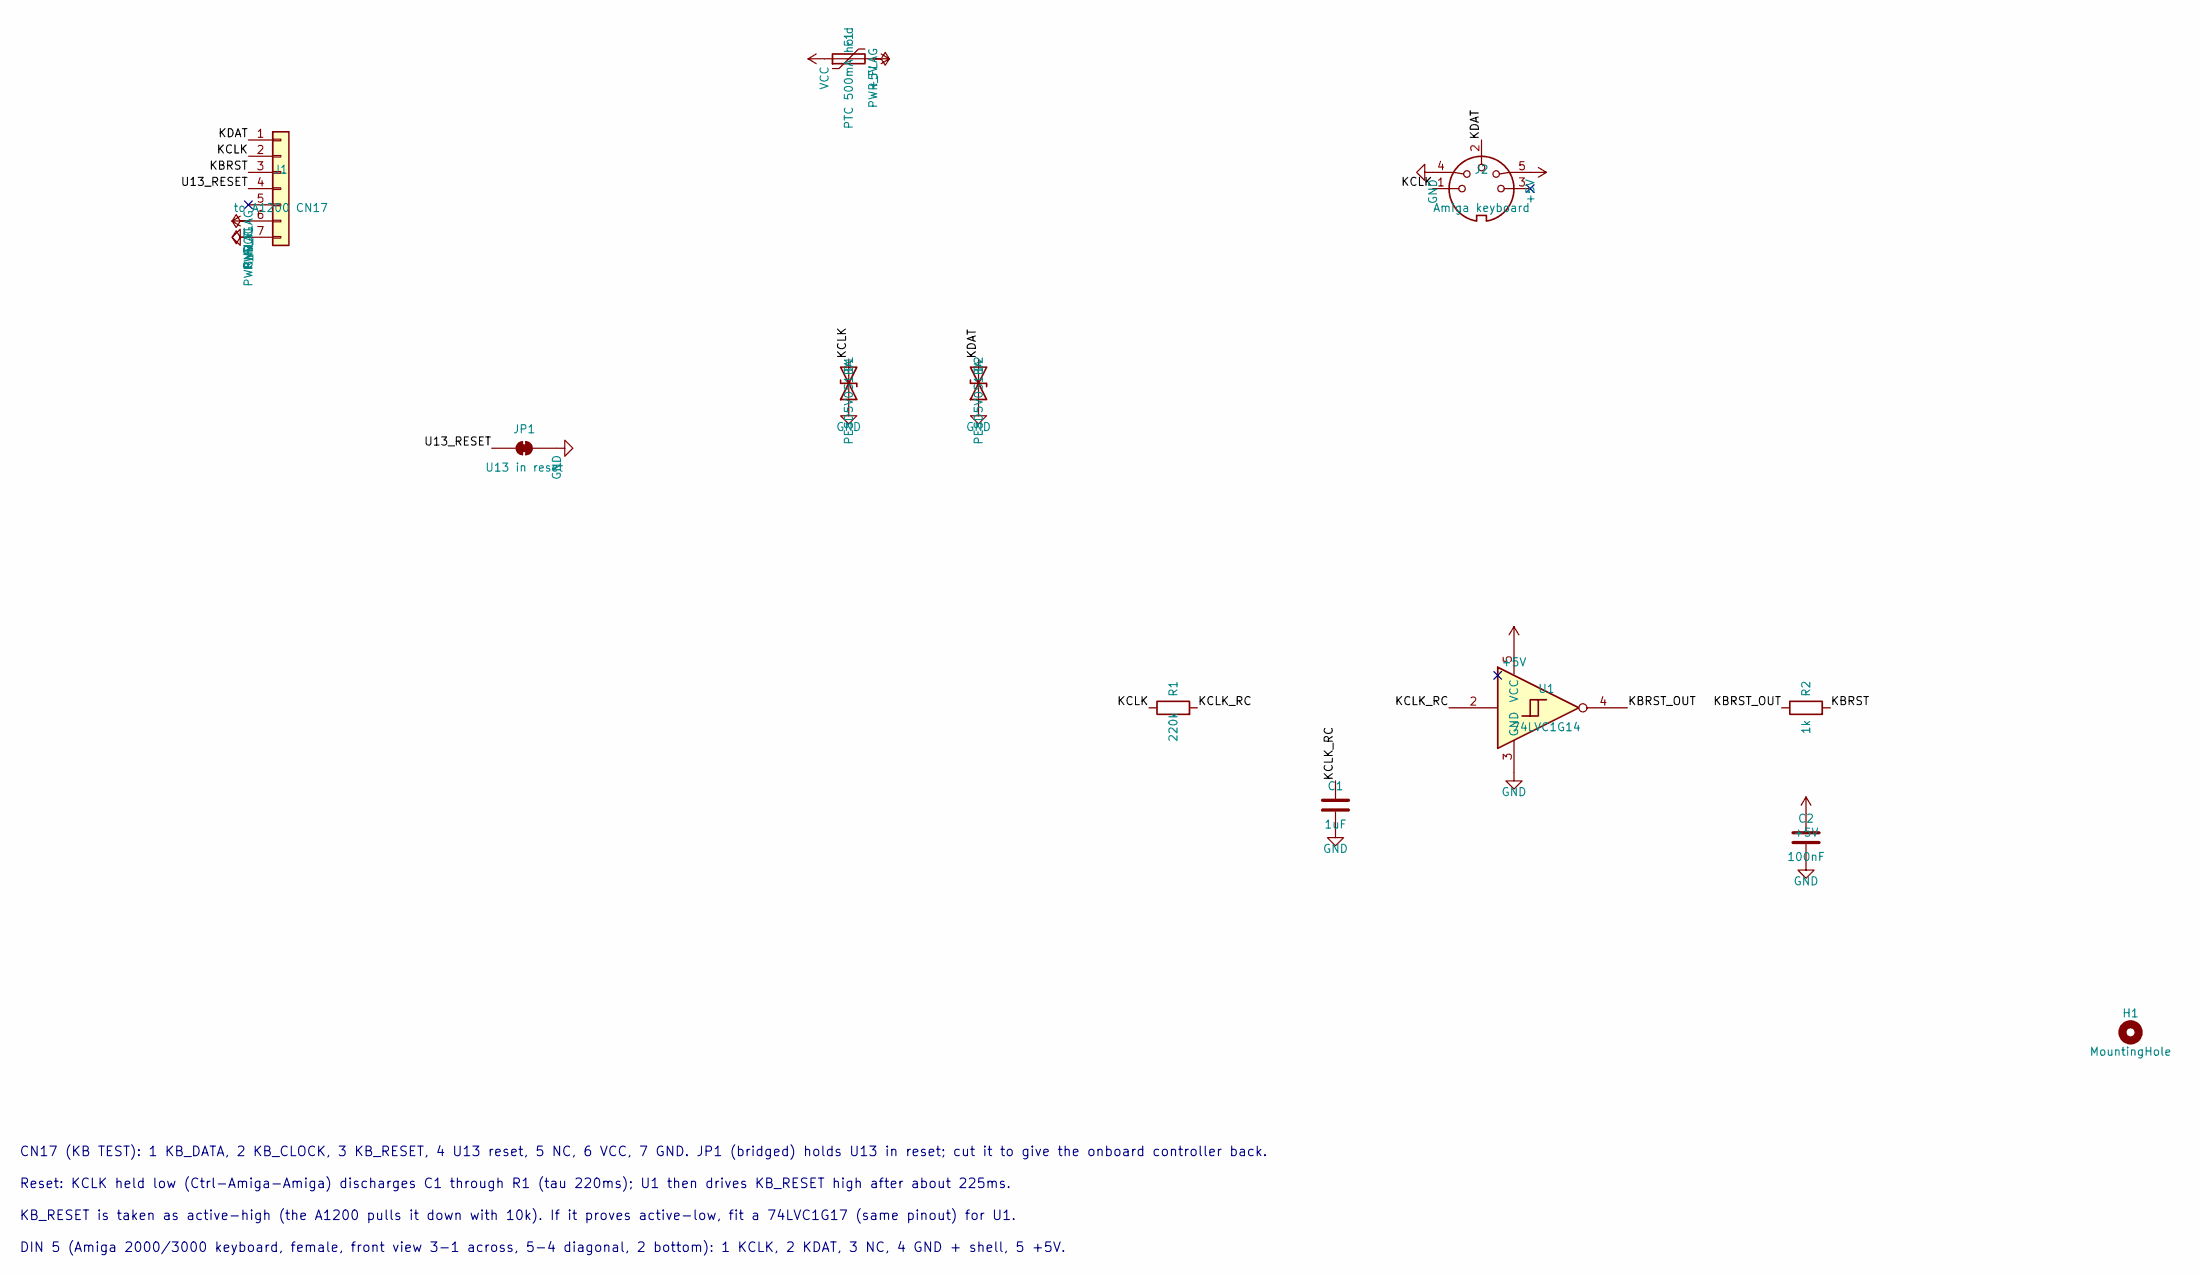
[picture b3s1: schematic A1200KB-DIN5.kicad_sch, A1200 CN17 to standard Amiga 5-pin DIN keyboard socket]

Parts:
C1: 1uF; C_0603_1608Metric; MPN CL10A105KB8NNNC; LCSC C15849
C2: 100nF; C_0603_1608Metric; MPN CC0603KRX7R9BB104; LCSC C14663
D1, D2: PESD5V0S1BA; D_SOD-323; MPN PESD5V0S1BA,115; LCSC C19224
F1: PTC 500mA hold; Fuse_1206_3216Metric; MPN nSMD050; LCSC C69688
H1: MountingHole; MountingHole_3.2mm_M3
J1: to A1200 CN17; PinHeader_1x07_P2.54mm_Vertical; MPN PZ254V-11-07P; LCSC C492406
J2: Amiga keyboard; DIN-5_180deg_DIN-504_Horizontal; MPN DIN-504; LCSC C23689428
JP1: U13 in reset; SolderJumper-2_P1.3mm_Bridged_RoundedPad1.0x1.5mm
R1: 220k; R_0603_1608Metric; MPN 0603WAF2203T5E; LCSC C22961
R2: 1k; R_0603_1608Metric; MPN 0603WAF1001T5E; LCSC C21190
U1: 74LVC1G14; SOT-353_SC-70-5; MPN 74LVC1G14GW,125; LCSC C265125

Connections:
+5V: C2.1, F1.2, J2.5, U1.5 (VCC)
/KBRST: J1.3, R2.2
/KBRST_OUT: R2.1, U1.4
/KCLK: D1.2 (A2), J1.2, J2.1, R1.1
/KCLK_RC: C1.1, R1.2, U1.2
/KDAT: D2.2 (A2), J1.1, J2.2
/U13_RESET: J1.4, JP1.1 (A)
GND: C1.2, C2.2, D1.1 (A1), D2.1 (A1), J1.7, J2.4, JP1.2 (B), U1.3 (GND)
VCC: F1.1, J1.6

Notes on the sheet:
CN17 (KB TEST): 1 KB_DATA, 2 KB_CLOCK, 3 KB_RESET, 4 U13 reset, 5 NC, 6 VCC, 7 GND. JP1 (bridged) holds U13 in reset; cut it to give the onboard controller back.
Reset: KCLK held low (Ctrl-Amiga-Amiga) discharges C1 through R1 (tau 220ms); U1 then drives KB_RESET high after about 225ms.
KB_RESET is taken as active-high (the A1200 pulls it down with 10k). If it proves active-low, fit a 74LVC1G17 (same pinout) for U1.
DIN 5 (Amiga 2000/3000 keyboard, female, front view 3-1 across, 5-4 diagonal, 2 bottom): 1 KCLK, 2 KDAT, 3 NC, 4 GND + shell, 5 +5V.

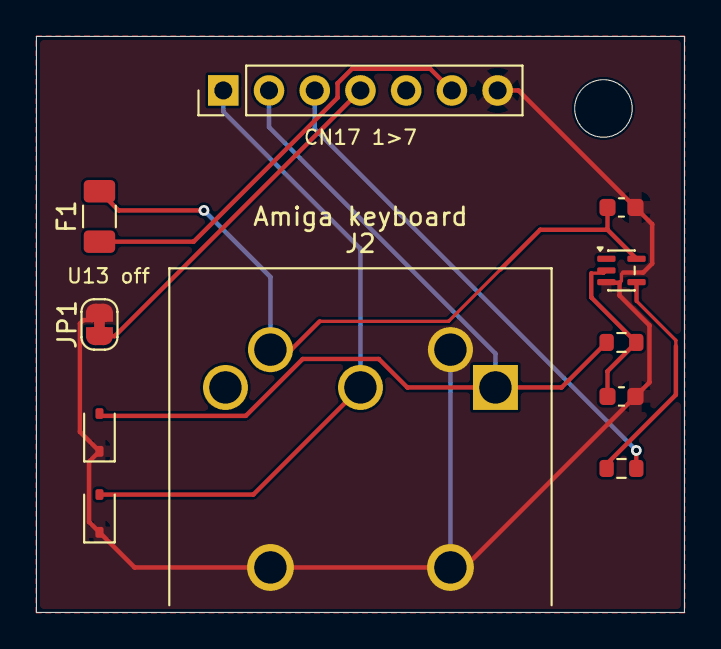
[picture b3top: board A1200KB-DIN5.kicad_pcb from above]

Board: 2 copper layers, 36.0 x 32.0 mm, 12 parts (0 on the bottom side), 9 nets.

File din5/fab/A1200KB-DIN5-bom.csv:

"Comment","Designator","Footprint","LCSC Part #","MPN"
"1uF","C1","Capacitor_SMD:C_0603_1608Metric","C15849","CL10A105KB8NNNC"
"100nF","C2","Capacitor_SMD:C_0603_1608Metric","C14663","CC0603KRX7R9BB104"
"PESD5V0S1BA","D1,D2","Diode_SMD:D_SOD-323","C19224","PESD5V0S1BA,115"
"PTC 500mA hold","F1","Fuse:Fuse_1206_3216Metric","C69688","nSMD050"
"to A1200 CN17","J1","Connector_PinHeader_2.54mm:PinHeader_1x07_P2.54mm_Vertical","C492406","PZ254V-11-07P"
"Amiga keyboard","J2","A1200KB:DIN-5_180deg_DIN-504_Horizontal","C23689428","DIN-504"
"220k","R1","Resistor_SMD:R_0603_1608Metric","C22961","0603WAF2203T5E"
"1k","R2","Resistor_SMD:R_0603_1608Metric","C21190","0603WAF1001T5E"
"74LVC1G14","U1","Package_TO_SOT_SMD:SOT-353_SC-70-5","C265125","74LVC1G14GW,125"

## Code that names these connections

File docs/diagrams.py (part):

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s = Svg(900, 420)
s.text(20, 28, 'A1200 side of the DIN 5 socket: CN17 only', 17, '#222', bold=True)
cn17 = s.pins(100, 55, ['KB_DATA', 'KB_CLOCK', 'KB_RESET', 'U13 reset', 'NC', 'VCC', 'GND'], 'right', AMIGA, 'A1200 CN17')
j1 = s.pins(620, 55, ['KDAT', 'KCLK', 'KB_RESET out', 'to JP1 (GND)', 'NC', 'VCC in', 'GND'], 'left', BOARD, 'din5 J1')
for p in range(1, 8):
    s.line(*cn17[p], *j1[p], '#333', 2.5)
s.text(450, 285, 'Straight 7-way cable, pin 1 to pin 1.', 13, '#222', 'middle', bold=True)
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# ---- no CN17: the same signals straight off U13 ----
s = Svg(900, 400)
s.text(20, 28, 'No CN17: take the same signals from U13 with a PLCC clip or piggyback', 17, '#222', bold=True)
u13 = s.pins(40, 55, ['pin 13 (PB0) KB_DATA', 'pin 14 (PB1) KB_CLOCK', 'pin 38 (TCMP) KB_RESET', 'pin 1 (/RESET)', '', 'pin 44 (VDD)', 'pin 22 (VSS)'], 'right', AMIGA, 'A1200 U13 (68HC05)', numbered=False, w=210)
j1 = s.pins(620, 55, ['KDAT', 'KCLK', 'KB_RESET out', 'to JP1 (GND)', 'NC', 'VCC in', 'GND'], 'left', BOARD, 'din5 J1')
for p in (1, 2, 3, 4, 6, 7):
    s.line(*u13[p], *j1[p], '#333', 2.5)
s.text(450, 285, 'Wire the clip to a 1x7 header in CN17 order, so the din5 board plugs straight in.', 13, '#222', 'middle', bold=True)
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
